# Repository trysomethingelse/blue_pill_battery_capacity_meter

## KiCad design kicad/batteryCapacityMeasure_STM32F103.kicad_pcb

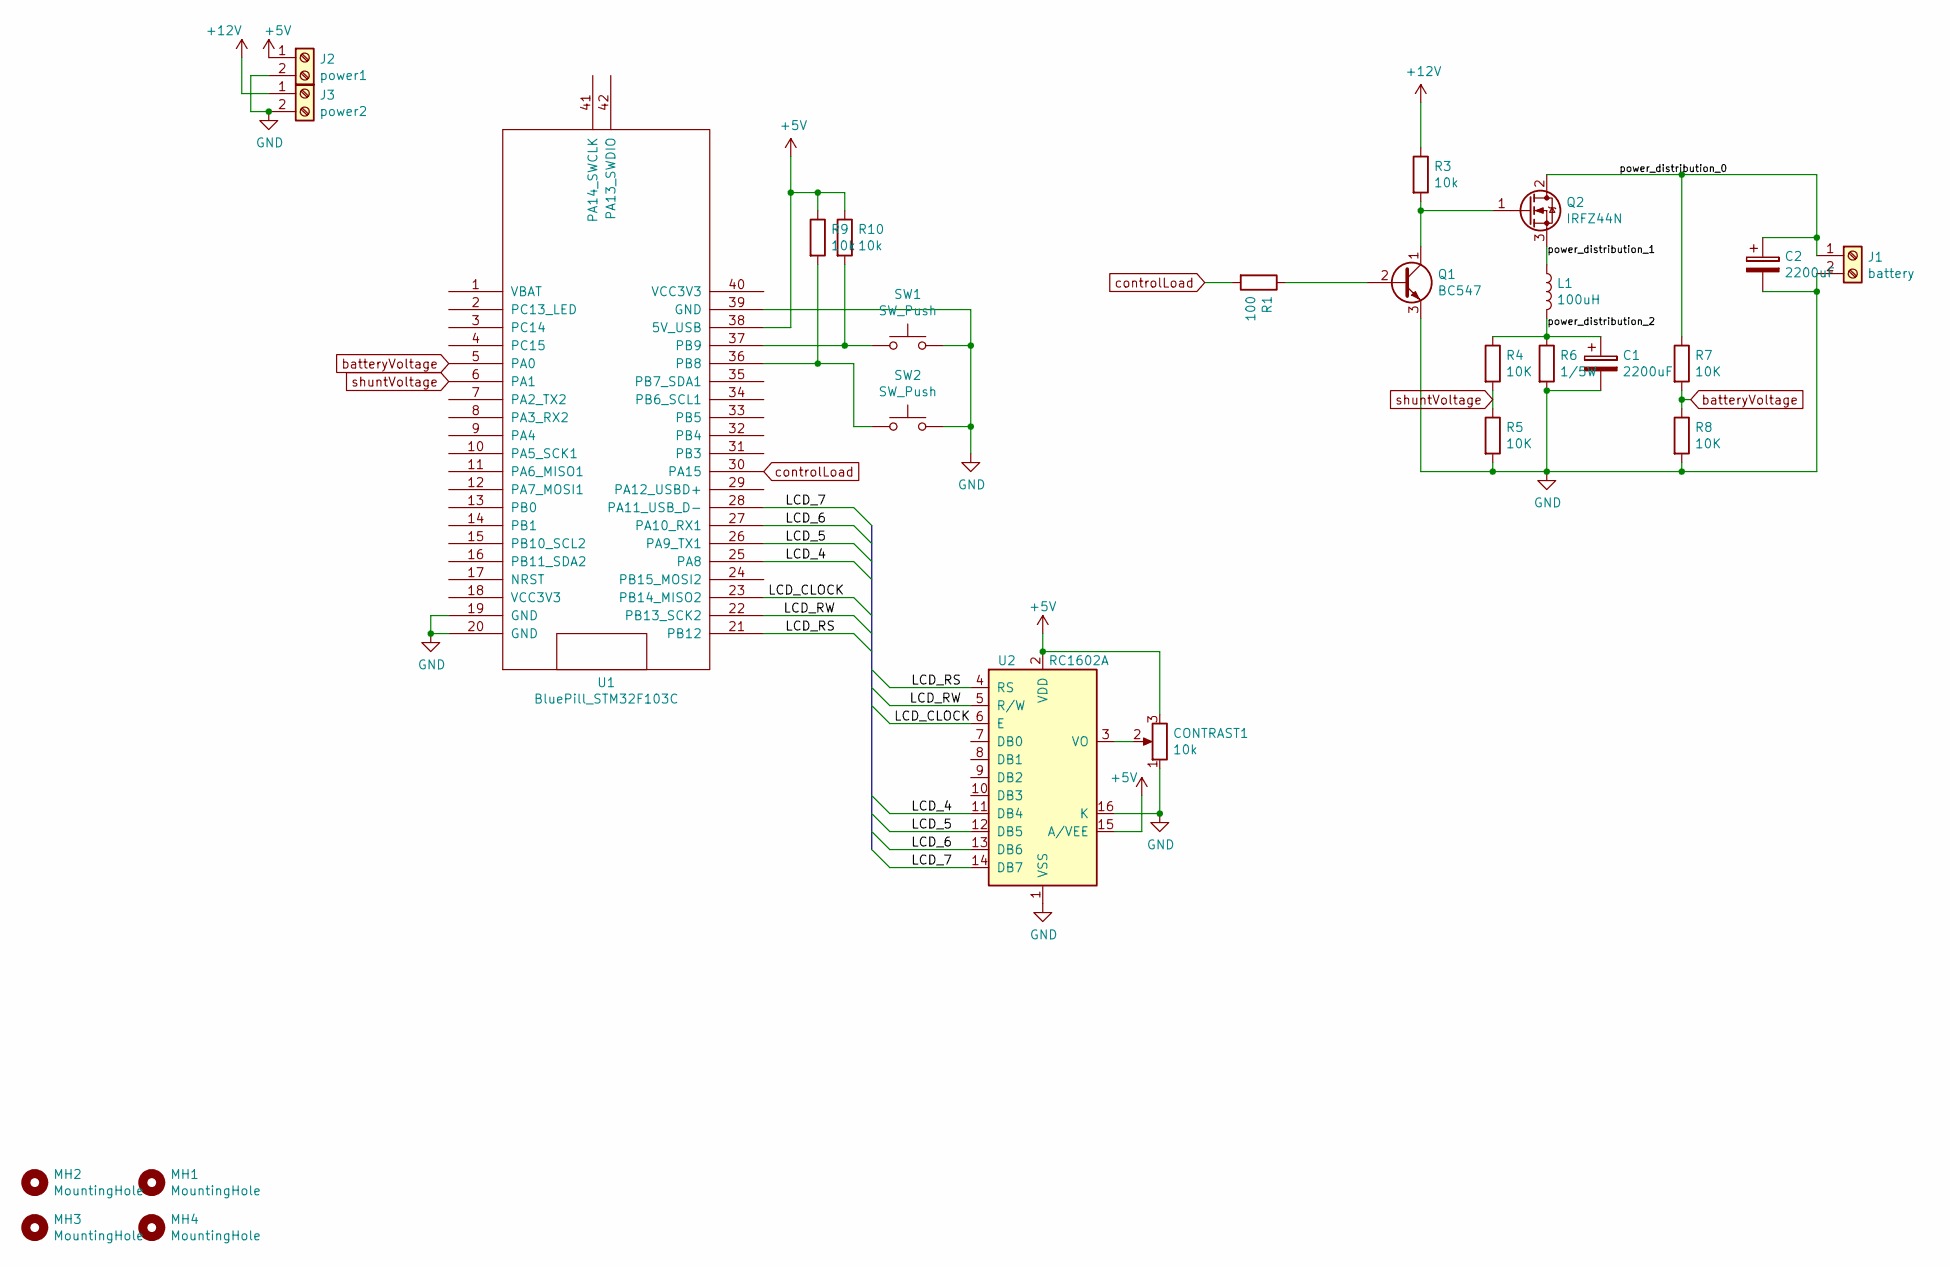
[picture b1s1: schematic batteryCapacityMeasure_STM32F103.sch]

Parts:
C1, C2: 2200uF; CP_Radial_D10.0mm_P7.50mm
CONTRAST1: 10k; Potentiometer_Trimmer_Piher_PT-10v10_Horizontal_Px10.0mm_Py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
J1: battery; TerminalBlock_bornier-2_P5.08mm
J2: power1; TerminalBlock_bornier-2_P5.08mm
J3: power2; TerminalBlock_bornier-2_P5.08mm
L1: 100uH; L_Radial_D7.5mm_P3.50mm_Fastron_07P
MH1, MH2, MH3, MH4: MountingHole; MountingHole_3.2mm_M3_Pad
Q1: BC547; TO-92_Inline_Wide
Q2: IRFZ44N; TO-220-3_Vertical
R1: 100; R_Axial_DIN0207_L6.3mm_D2.5mm_P7.62mm_Horizontal
R3, R9, R10: 10k; R_Axial_DIN0207_L6.3mm_D2.5mm_P7.62mm_Horizontal
R4, R5, R7, R8: 10K; R_Axial_DIN0207_L6.3mm_D2.5mm_P7.62mm_Horizontal
R6: 1/5W; power_resisor_7W
SW1, SW2: SW_Push; SW_PUSH_6mm_h7.3mm
U1: BluePill_STM32F103C; bluepill_dip40_stm32f103c8
U2: RC1602A; lcd_1602A

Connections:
+5V: CONTRAST1.3, J2.1, R9.1, R10.1, U1.38 (5V_USB), U2.2 (VDD), U2.15 (A/VEE)
+12V: J3.1, R3.1
/LCD_4: U1.25 (PA8), U2.11 (DB4)
/LCD_5: U1.26 (PA9_TX1), U2.12 (DB5)
/LCD_6: U1.27 (PA10_RX1), U2.13 (DB6)
/LCD_7: U1.28 (PA11_USB_D-), U2.14 (DB7)
/LCD_CLOCK: U1.23 (PB14_MISO2), U2.6 (E)
/LCD_RS: U1.21 (PB12), U2.4 (RS)
/LCD_RW: U1.22 (PB13_SCK2), U2.5 (R/W)
/power_distribution_0: C2.1, J1.1, Q2.2 (D), R7.1
/power_distribution_1: L1.1, Q2.3 (S)
/power_distribution_2: C1.1, L1.2, R4.1, R6.1
GND: C1.2, C2.2, CONTRAST1.1, J1.2, J2.2, J3.2, Q1.3 (E), R5.2, R6.2, R8.2, SW1.2, SW2.2, U1.19 (GND), U1.20 (GND), U1.39 (GND), U2.1 (VSS), U2.16 (K)
unnamed: CONTRAST1.2, U2.3 (VO)
unnamed: Q1.1 (C), Q2.1 (G), R3.2
unnamed: Q1.2 (B), R1.1
unnamed: R9.2, SW2.1, U1.36 (PB8)
unnamed: R10.2, SW1.1, U1.37 (PB9)
batteryVoltage: R7.2, R8.1, U1.5 (PA0)
controlLoad: R1.2, U1.30 (PA15)
shuntVoltage: R4.2, R5.1, U1.6 (PA1)

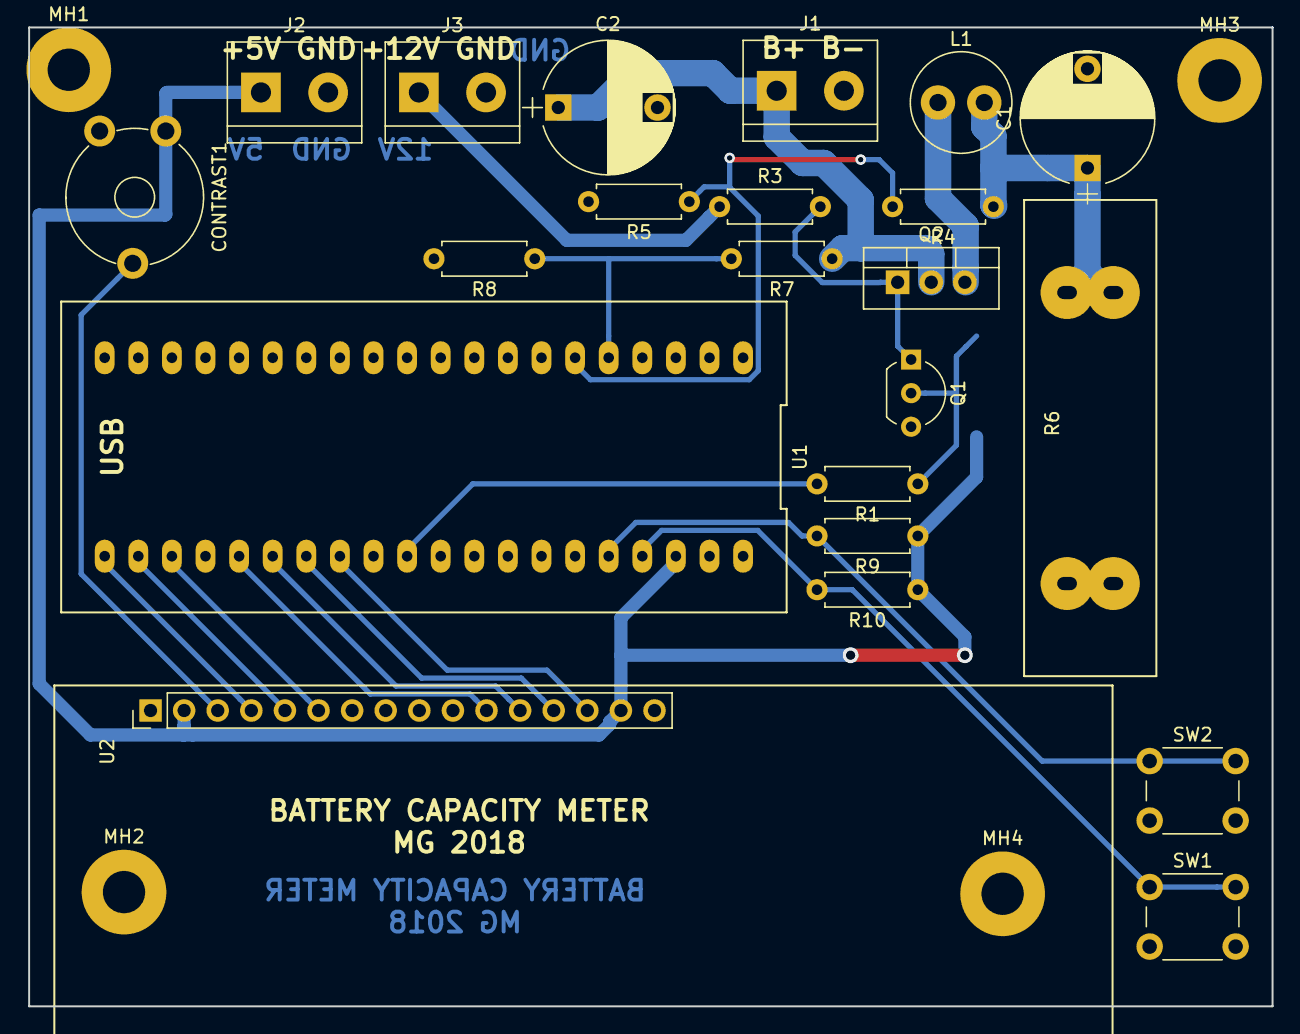
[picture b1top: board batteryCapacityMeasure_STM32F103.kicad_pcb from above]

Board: 2 copper layers, 94.0 x 74.0 mm, 26 parts (0 on the bottom side), 21 nets.

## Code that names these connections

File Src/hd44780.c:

#include "hd44780.h"

uint8_t busy_flag_check()
{

	uint8_t out = BUSY;

	//must to set all data lines as input
	GPIO_InitTypeDef GPIO_InitStruct;
	GPIO_InitStruct.Pin = LCD_4567;
	GPIO_InitStruct.Mode = GPIO_MODE_INPUT;
	HAL_GPIO_Init(LCD_DATA_PORT, &GPIO_InitStruct);
	HAL_GPIO_WritePin(LCD_CONTROL_PORT,LCD_RW,GPIO_PIN_SET);//read from lcd
	HAL_GPIO_WritePin(LCD_DATA_PORT,LCD_RS,GPIO_PIN_RESET);
	HAL_GPIO_WritePin(LCD_CONTROL_PORT,LCD_CLOCK,GPIO_PIN_SET);

	for(int i = NO_BUSY_CHECK; i >  0; i-- )
	{
		if(HAL_GPIO_ReadPin(LCD_DATA_PORT,LCD_7) == NOT_BUSY)
		{
			out = NOT_BUSY;
			break;
		}

	}

	//set data lines as output
	GPIO_InitStruct.Pin = LCD_4567;
	GPIO_InitStruct.Mode = GPIO_MODE_OUTPUT_PP;
	GPIO_InitStruct.Speed = GPIO_SPEED_FREQ_HIGH;
	HAL_GPIO_Init(LCD_DATA_PORT, &GPIO_InitStruct);
	HAL_GPIO_WritePin(LCD_CONTROL_PORT,LCD_RW,GPIO_PIN_RESET);//write to lcd
	//HAL_GPIO_WritePin(LCD_CONTROL_PORT,LCD_CLOCK,GPIO_PIN_RESET);



	return out;
}


uint8_t lcd_print(char word[])
{
	for(int i = 0; word[i] != 0; i++)
	{
		if(lcd_print_letter(word[i]) == COMMAND_BUSY_ERROR)return COMMAND_BUSY_ERROR;
	}
	return COMMAND_SUCCESS;
}
uint8_t lcd_print_int(int number)
{
	char word[sizeof(int)];
	sprintf(word,"%d",number);
	return lcd_print(word);
}

uint8_t lcd_print_double(double number,uint8_t precision)
{
	char word[sizeof(int)];
	gcvt(number,precision, word);
	return lcd_print(word);
}
uint8_t lcd_print_letter(uint8_t letter)
{

	if (busy_flag_check() == BUSY) return COMMAND_BUSY_ERROR;
	lcd_write_nibble(letter,MSB, 1);
	lcd_write_nibble(letter,LSB, 1);
	return COMMAND_SUCCESS;
}

void lcd_init()
{
	if (busy_flag_check() != BUSY)
	{
		lcd_write_nibble(SET_4BIT_OPERATION,MSB,0);
		lcd_write(TWO_LINES_4BIT);
		lcd_write(DISPLAY_ON_OFF);
		lcd_write(ENTRY_MODE_INCREMENT | DISPLAY_SHIFT_OFF);
	}
}
void lcd_write_nibble(uint8_t command, uint8_t start_bit, uint8_t rs)
{
	uint32_t bsrr = 0;

	if (get_bit(command,start_bit)) bsrr |= LCD_7; //set one
	else bsrr |= ((uint32_t)LCD_7 <<16U);  //must to shift to left, because of BSRR from 16 place resets ODR

	if (get_bit(command,start_bit-1)) bsrr |= LCD_6; //set one
	else bsrr |= ((uint32_t)LCD_6 <<16U);  //must to shift to left, because of BSRR from 16 place resets ODR

	if (get_bit(command,start_bit-2)) bsrr |= LCD_5; //set one
	else bsrr |= ((uint32_t)LCD_5 <<16U);  //must to shift to left, because of BSRR from 16 place resets ODR

	if (get_bit(command,start_bit-3)) bsrr |= LCD_4; //set one
	else bsrr |= ((uint32_t)LCD_4 << 16U);  //must to shift to left, because of BSRR from 16 place resets ODR

	LCD_DATA_PORT -> BSRR =  bsrr;


	bsrr = 0;
	bsrr = LCD_RW << 16U; //set zero on RW
	if (rs) bsrr |= LCD_RS; //set one
	else bsrr |= LCD_RS << 16U;  //must to shift to left, because of BSRR from 16 place resets ODR
	LCD_CONTROL_PORT -> BSRR = bsrr;

	lcd_clock();

}
uint8_t lcd_write(uint8_t command)
{
	if (busy_flag_check() == BUSY) return COMMAND_BUSY_ERROR;
	lcd_write_nibble(command,MSB, 0);
	lcd_write_nibble(command,LSB, 0);
	return COMMAND_SUCCESS;
}
uint8_t get_bit(uint8_t command, uint8_t no)
{
	return ((command >> no) & 1);
}
void lcd_clock()
{
	HAL_GPIO_WritePin(LCD_CONTROL_PORT, LCD_CLOCK,GPIO_PIN_SET);
	HAL_Delay(1);
	HAL_GPIO_WritePin(LCD_CONTROL_PORT, LCD_CLOCK,GPIO_PIN_RESET);
	HAL_Delay(1);
}

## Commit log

2018-12-09 nothing works, but template is there
2018-12-10 displaing time and interupts for switches
2018-12-12 timer3 works
2018-12-12 adc only for one channel
    working on injected mode
2018-12-13 two independent ADCs working
2018-12-14 integrating of energy
    result is quite good, but can be improved in numerical errors
2018-12-15 timer 3 agrees with rtc
2018-12-15 integrating of energy is correct
    more tests required
2018-12-15 pwm is running
    todo make variable pwm
2018-12-16 control of current works, measuring battery works
2018-12-16 debounce applied
2018-12-18 18650 measuring implementation - not quite good
2019-02-11 improved measuring of 18650 cell, measuring in mAh for 18650, pause and reset works good
2019-02-13 changed min battery voltage, improved lcd
2019-02-23 18650 added const current discharge
2019-02-23 fixed discharging current after end of measure
2019-02-24 now current is adjusted in given interval, code gruped to more functions
2019-11-14 added pcb, tiding
